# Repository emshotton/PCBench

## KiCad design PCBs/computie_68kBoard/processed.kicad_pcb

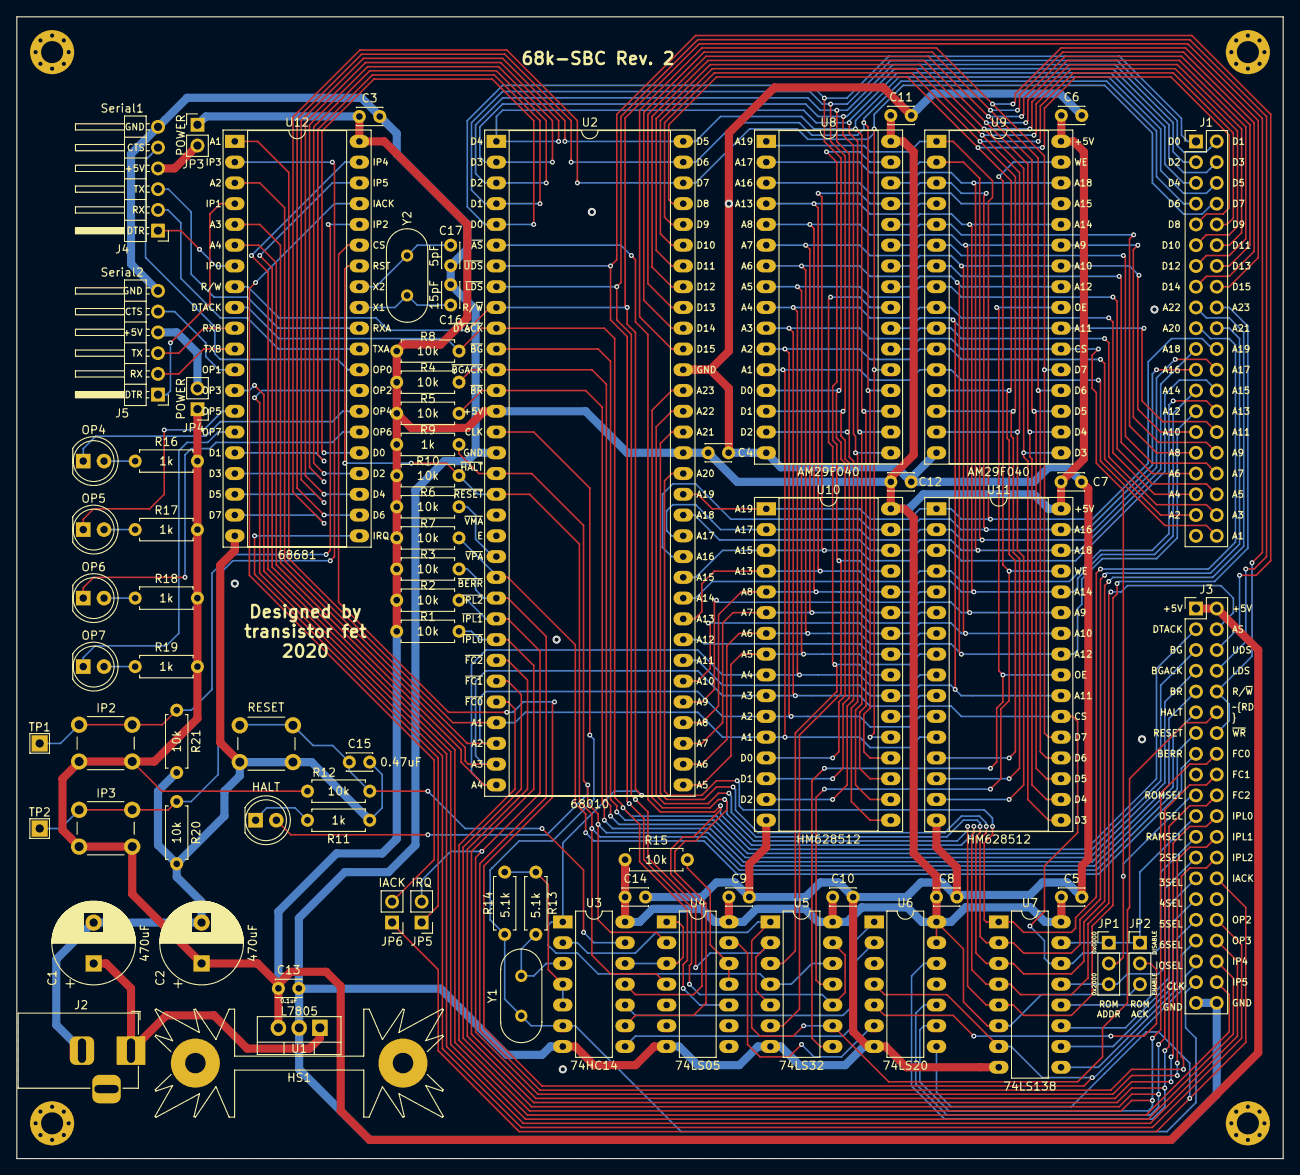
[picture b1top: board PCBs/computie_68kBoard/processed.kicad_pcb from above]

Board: 2 copper layers, 154.9 x 139.7 mm, 78 parts (0 on the bottom side), 114 nets.

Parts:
C1, C2: 470uF; CP_Radial_D10.0mm_P5.00mm
C3, C4, C5, C6, C7, C8, C9, C10, C11, C12, C13, C14: 0.1uF; C_Disc_D3.0mm_W2.0mm_P2.50mm
C15: 0.47uF; C_Disc_D3.0mm_W2.0mm_P2.50mm
C16: 15pF; C_Disc_D3.0mm_W2.0mm_P2.50mm
C17: 5pF; C_Disc_D3.0mm_W2.0mm_P2.50mm
D1: HALT; LED_D5.0mm
D2: OP4; LED_D5.0mm
D3: OP5; LED_D5.0mm
D4: OP6; LED_D5.0mm
D5: OP7; LED_D5.0mm
H1, H2, H3, H4: .; MountingHole_2.7mm_Pad_Via
HS1: Heatsink; Heatsink_Fischer_SK104-STC-STIC_35x13mm_2xDrill2.5mm
J1: ADBUS; PinHeader_2x20_P2.54mm_Vertical
J2: Barrel_Jack; BarrelJack_Horizontal
J3: SIGBUS; PinHeader_2x20_P2.54mm_Vertical
J4: Serial1; PinHeader_1x06_P2.54mm_Horizontal
J5: Serial2; PinHeader_1x06_P2.54mm_Horizontal
JP1: ROMJMP; PinHeader_1x03_P2.54mm_Vertical
JP2: ROMACK; PinHeader_1x03_P2.54mm_Vertical
JP3, JP4: POWER; PinHeader_1x02_P2.54mm_Vertical
JP5: IRQ; PinHeader_1x02_P2.54mm_Vertical
JP6: IACK; PinHeader_1x02_P2.54mm_Vertical
R1, R2, R3, R4, R5, R6, R7, R8, R10, R12, R15, R20, R21: 10k; R_Axial_DIN0207_L6.3mm_D2.5mm_P7.62mm_Horizontal
R9, R11, R16, R17, R18, R19: 1k; R_Axial_DIN0207_L6.3mm_D2.5mm_P7.62mm_Horizontal
R13, R14: 5.1k; R_Axial_DIN0207_L6.3mm_D2.5mm_P7.62mm_Horizontal
SW1: RESET; SW_PUSH_6mm
SW2: IP2; SW_PUSH_6mm
SW3: IP3; SW_PUSH_6mm
TP1: IP2; TestPoint_THTPad_2.0x2.0mm_Drill1.0mm
TP2: IP3; TestPoint_THTPad_2.0x2.0mm_Drill1.0mm
U1: L7805; TO-220-3_Vertical
U2: 68010; DIP-64_W22.86mm_Socket_LongPads
U3: 74HC14; DIP-14_W7.62mm_LongPads
U4: 74LS05; DIP-14_W7.62mm_LongPads
U5: 74LS32; DIP-14_W7.62mm_LongPads
U6: 74LS20; DIP-14_W7.62mm_LongPads
U7: 74LS138; DIP-16_W7.62mm_LongPads
U8, U9: AM29F040; DIP-32_W15.24mm_Socket_LongPads
U10, U11: HM628512; DIP-32_W15.24mm_Socket_LongPads
U12: 68681; DIP-40_W15.24mm_Socket_LongPads
Y1, Y2: Crystal; Crystal_HC49-4H_Vertical

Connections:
0SEL: J3.21, JP1.1, JP2.1, U7.15
2SEL: J3.25, JP1.3, U7.13
3SEL: J3.27, U7.12
4SEL: J3.29, U7.11
5SEL: J3.31, U7.10
6SEL: J3.33, U7.9
+5V: C2.1, C3.1, C4.1, C5.1, C6.1, C7.1, C8.1, C9.1, C10.1, C11.1, C12.1, C13.1, C14.1, J3.1, J3.2, JP2.3, JP3.1, JP4.1, R1.1, R2.1, R3.1, R4.1, R5.1, R6.1, R7.1, R8.1, R9.1, R10.1, R12.1, R15.1, R16.2, R17.2, R18.2, R19.2, SW2.2, SW3.2, U1.3, U2.14, U2.49, U3.14, U4.14, U5.14, U6.13, U6.14, U7.6, U7.16, U8.32, U9.32, U10.32, U11.32, U12.40
A1: J1.40, U2.29, U8.12, U9.12, U10.12, U11.12, U12.1
A2: J1.37, U2.30, U8.11, U9.11, U10.11, U11.11, U12.3
A3: J1.38, U2.31, U8.10, U9.10, U10.10, U11.10, U12.5
A4: J1.35, U2.32, U8.9, U9.9, U10.9, U11.9, U12.6
A5: J1.36, U2.33, U8.8, U9.8, U10.8, U11.8
A6: J1.33, U2.34, U8.7, U9.7, U10.7, U11.7
A7: J1.34, U2.35, U8.6, U9.6, U10.6, U11.6
A8: J1.31, U2.36, U8.5, U9.5, U10.5, U11.5
A9: J1.32, U2.37, U8.27, U9.27, U10.27, U11.27
A10: J1.29, U2.38, U8.26, U9.26, U10.26, U11.26
A11: J1.30, U2.39, U8.23, U9.23, U10.23, U11.23
A12: J1.27, U2.40, U8.25, U9.25, U10.25, U11.25
A13: J1.28, U2.41, U8.4, U9.4, U10.4, U11.4
A14: J1.25, U2.42, U8.28, U9.28, U10.28, U11.28
A15: J1.26, U2.43, U8.29, U9.29, U10.3, U11.3
A16: J1.23, U2.44, U8.3, U9.3, U10.31, U11.31
A17: J1.24, U2.45, U8.2, U9.2, U10.2, U11.2
A18: J1.21, U2.46, U8.30, U9.30, U10.30, U11.30
A19: J1.22, U2.47, U8.1, U9.1, U10.1, U11.1
A20: J1.19, U2.48, U7.1
A21: J1.20, U2.50, U7.2
A22: J1.17, U2.51, U7.3
A23: J1.18, U2.52, U3.9, U7.5
AS: J3.4, U2.6, U3.11, U7.4
BERR: J3.15, R7.2, U2.22
BG: J3.5, U2.11
BGACK: J3.7, R4.2, U2.12
BR: J3.9, R5.2, U2.13
CLK: J3.37, R14.1, U2.15, U3.6, Y1.2
D0: J1.1, U2.5, U8.13, U10.13, U12.25
D1: J1.2, U2.4, U8.14, U10.14, U12.16
D2: J1.3, U2.3, U8.15, U10.15, U12.24
D3: J1.4, U2.2, U8.17, U10.17, U12.17
D4: J1.5, U2.1, U8.18, U10.18, U12.23
D5: J1.6, U2.64, U8.19, U10.19, U12.18
D6: J1.7, U2.63, U8.20, U10.20, U12.22
D7: J1.8, U2.62, U8.21, U10.21, U12.19
D8: J1.9, U2.61, U9.13, U11.13
D9: J1.10, U2.60, U9.14, U11.14
D10: J1.11, U2.59, U9.15, U11.15
D11: J1.12, U2.58, U9.17, U11.17
D12: J1.13, U2.57, U9.18, U11.18
D13: J1.14, U2.56, U9.19, U11.19
D14: J1.15, U2.55, U9.20, U11.20
D15: J1.16, U2.54, U9.21, U11.21
DTACK: J3.3, R8.2, U2.10, U4.10, U12.9
FC0: J3.16, U2.28, U6.9
FC1: J3.18, U2.27, U6.10
FC2: J3.20, U2.26, U6.12
GND: C1.2, C2.2, C3.2, C4.2, C5.2, C6.2, C7.2, C8.2, C9.2, C10.2, C11.2, C12.2, C13.2, C14.2, C15.2, C16.1, C17.1, J2.2, J3.39, J3.40, J4.6, J5.6, R11.2, R20.2, R21.2, SW1.1, U1.2, U2.16, U2.53, U3.7, U4.7, U5.7, U6.7, U7.8, U8.16, U9.16, U10.16, U11.16, U12.20
HALT: D1.2, J3.11, R9.2, U2.17, U4.2
IACK: J3.28, JP6.1, U6.8
IOSEL: J3.35, U6.4, U7.7, U12.35
IP4: J3.36, U12.39
IP5: J3.38, U12.38
IPL0: J3.22, R1.2, U2.25
IPL1: J3.24, JP5.2, R2.2, U2.24
IPL2: J3.26, R3.2, U2.23
LDS: J3.8, U2.8, U5.2, U5.5
unnamed: C1.1, J2.1, U1.1
unnamed: C15.1, R12.2, SW1.2, U3.13
unnamed: C16.2, U12.32, Y2.2
unnamed: C17.2, U12.33, Y2.1
unnamed: D1.1, R11.1
unnamed: D2.1, U12.27
unnamed: D2.2, R16.1
unnamed: D3.1, U12.14
unnamed: D3.2, R17.1
unnamed: D4.1, U12.26
unnamed: D4.2, R18.1
unnamed: D5.1, U12.15
unnamed: D5.2, R19.1
unnamed: J4.1, U12.7
unnamed: J4.2, U12.30
unnamed: J4.3, U12.31
unnamed: J4.4, JP3.2
unnamed: J4.5, U12.29
unnamed: J5.1, U12.4
unnamed: J5.2, U12.11
unnamed: J5.3, U12.10
unnamed: J5.4, JP4.2
unnamed: J5.5, U12.12
unnamed: JP2.2, U6.5
unnamed: R6.2, U2.21
unnamed: R13.1, R14.2, U3.4, U3.5
unnamed: R13.2, U3.3, Y1.1
unnamed: R15.2, U4.11, U4.12
unnamed: R20.1, SW3.1, TP2.1, U12.2
unnamed: R21.1, SW2.1, TP1.1, U12.36
unnamed: U3.8, U6.2
unnamed: U3.10, U6.1
unnamed: U3.12, U4.1, U4.3
unnamed: U4.13, U6.6
OP2: J3.32, U12.28
OP3: J3.34, U12.13
RAMSEL: J3.23, U7.14, U10.22, U11.22
RD: J3.12, U3.2, U5.1, U5.9
RD-L: U5.3, U8.24, U10.24
RD-U: U5.8, U9.24, U11.24
RESET: J3.13, R10.2, U2.18, U4.4, U12.34
ROMSEL: J3.19, JP1.2, U8.22, U9.22
R~W: J3.10, J3.14, U2.9, U3.1, U5.4, U5.12, U12.8
SIACK: JP6.2, U12.37
SIRQ: JP5.1, U12.21
UDS: J3.6, U2.7, U5.10, U5.13
WR-L: U5.6, U8.31, U10.29
WR-U: U5.11, U9.31, U11.29

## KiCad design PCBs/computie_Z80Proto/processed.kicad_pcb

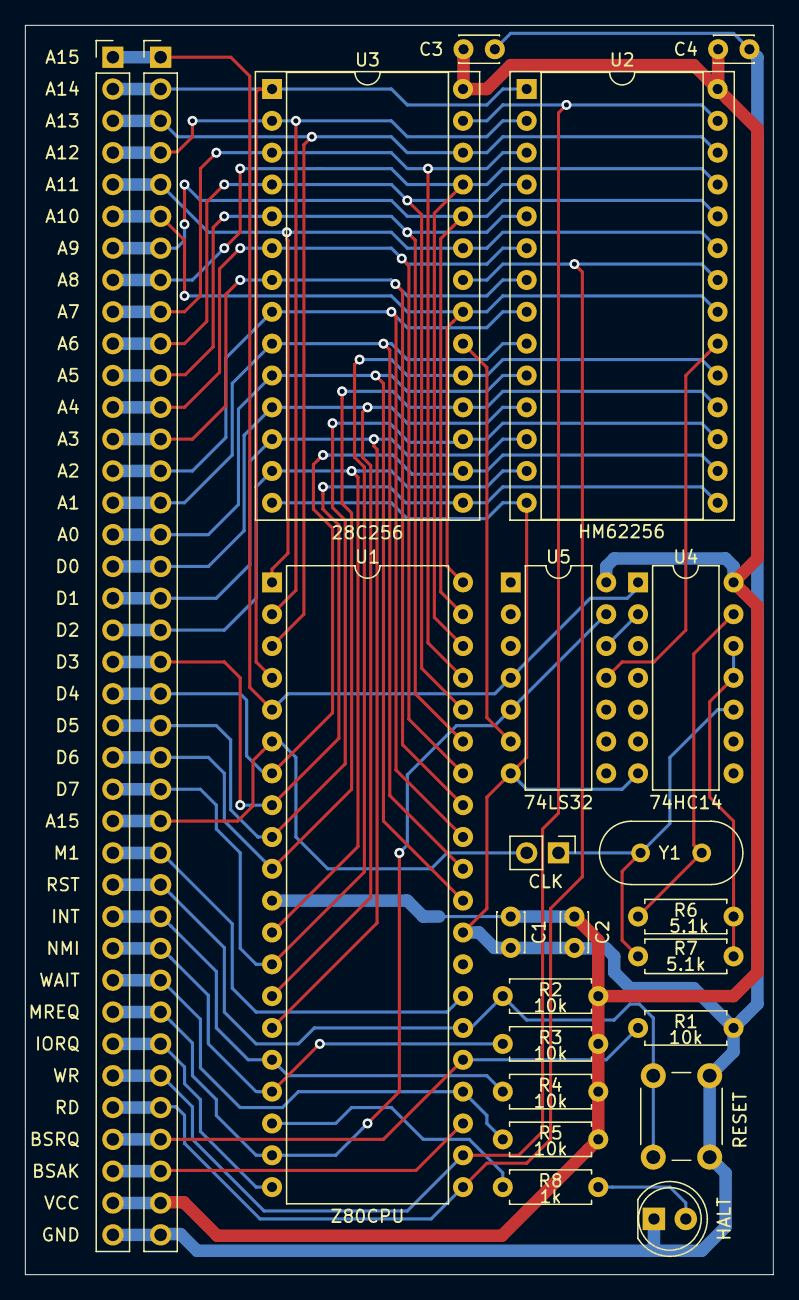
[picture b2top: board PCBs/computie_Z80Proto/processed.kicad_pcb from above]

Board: 2 copper layers, 59.7 x 99.7 mm, 23 parts (0 on the bottom side), 46 nets.

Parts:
B1: RESET; SW_PUSH_6mm
C1, C3, C4: 0.1uF; C_Disc_D3.0mm_W2.0mm_P2.50mm
C2: 0.47uF; C_Disc_D3.0mm_W2.0mm_P2.50mm
J1, J1#2: Conn_01x38; PinHeader_1x38_P2.54mm_Vertical
JP1: CLK; PinHeader_1x02_P2.54mm_Vertical
LED1: HALT; LED_D5.0mm
R1, R2, R3, R4, R5: 10k; R_Axial_DIN0207_L6.3mm_D2.5mm_P7.62mm_Horizontal
R6, R7: 5.1k; R_Axial_DIN0207_L6.3mm_D2.5mm_P7.62mm_Horizontal
R8: 1k; R_Axial_DIN0207_L6.3mm_D2.5mm_P7.62mm_Horizontal
U1: Z80CPU; DIP-40_W15.24mm
U2: HM62256; DIP-28_W15.24mm_Socket
U3: 28C256; DIP-28_W15.24mm_Socket
U4: 74HC14; DIP-14_W7.62mm
U5: 74LS32; DIP-14_W7.62mm
Y1: Crystal; Crystal_HC49-4H_Vertical

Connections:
/A0: J1.16, J1#2.16, U1.30, U2.10, U3.10
/A1: J1.15, J1#2.15, U1.31, U2.9, U3.9
/A2: J1.14, J1#2.14, U1.32, U2.8, U3.8
/A3: J1.13, J1#2.13, U1.33, U2.7, U3.7
/A4: J1.12, J1#2.12, U1.34, U2.6, U3.6
/A5: J1.11, J1#2.11, U1.35, U2.5, U3.5
/A6: J1.10, J1#2.10, U1.36, U2.4, U3.4
/A7: J1.9, J1#2.9, U1.37, U2.3, U3.3
/A8: J1.8, J1#2.8, U1.38, U2.25, U3.25
/A9: J1.7, J1#2.7, U1.39, U2.24, U3.24
/A10: J1.6, J1#2.6, U1.40, U2.21, U3.21
/A11: J1.5, J1#2.5, U1.1, U2.23, U3.23
/A12: J1.4, J1#2.4, U1.2, U2.2, U3.2
/A13: J1.3, J1#2.3, U1.3, U2.26, U3.26
/A14: J1.2, J1#2.2, U1.4, U2.1, U3.1
/A15: J1.1, J1#2.1, U1.5, U4.1, U5.4
/D0: J1.17, J1#2.17, U1.14, U2.11, U3.11
/D1: J1.18, J1#2.18, U1.15, U2.12, U3.12
/D2: J1.19, J1#2.19, U1.12, U2.13, U3.13
/D3: J1.20, J1#2.20, U1.8, U2.15, U3.15
/D4: J1.21, J1#2.21, U1.7, U2.16, U3.16
/D5: J1.22, J1#2.22, U1.9, U2.17, U3.17
/D6: J1.23, J1#2.23, U1.10, U2.18, U3.18
/D7: J1.24, J1#2.24, U1.13, U2.19, U3.19
BUSACK: J1.36, J1#2.36, U1.23
BUSREQ: J1.35, J1#2.35, R1.1, U1.25
CLK: J1.25, J1#2.25, JP1.2, U1.6
GND: B1.1, C1.2, C2.2, C3.2, C4.2, J1.38, J1#2.38, LED1.1, R1.2, U1.29, U2.14, U3.14, U4.7, U5.7
HALT: R8.1, U1.18
INT: J1.28, J1#2.28, R4.2, U1.16
IOREQ: J1.32, J1#2.32, U1.20
M1: J1.26, J1#2.26, U1.27
MREQ: J1.31, J1#2.31, U1.19, U5.5, U5.13
NMI: J1.29, J1#2.29, R3.2, U1.17
unnamed: JP1.1, R7.1, U4.10, Y1.2
unnamed: LED1.2, R8.2
unnamed: R6.1, R7.2, U4.11, U4.12
unnamed: R6.2, U4.13, Y1.1
unnamed: U2.20, U5.11
unnamed: U3.20, U5.6
unnamed: U4.2, U5.12
RD: J1.34, J1#2.34, U1.21, U2.22, U3.22
RESET: B1.2, J1.27, J1#2.27, R2.2, U1.26
Vcc: C1.1, C2.1, C3.1, C4.1, J1.37, J1#2.37, R2.1, R3.1, R4.1, R5.1, U1.11, U2.28, U3.28, U4.14, U5.14
WAIT: J1.30, J1#2.30, R5.2, U1.24
WR: J1.33, J1#2.33, U1.22, U2.27, U3.27

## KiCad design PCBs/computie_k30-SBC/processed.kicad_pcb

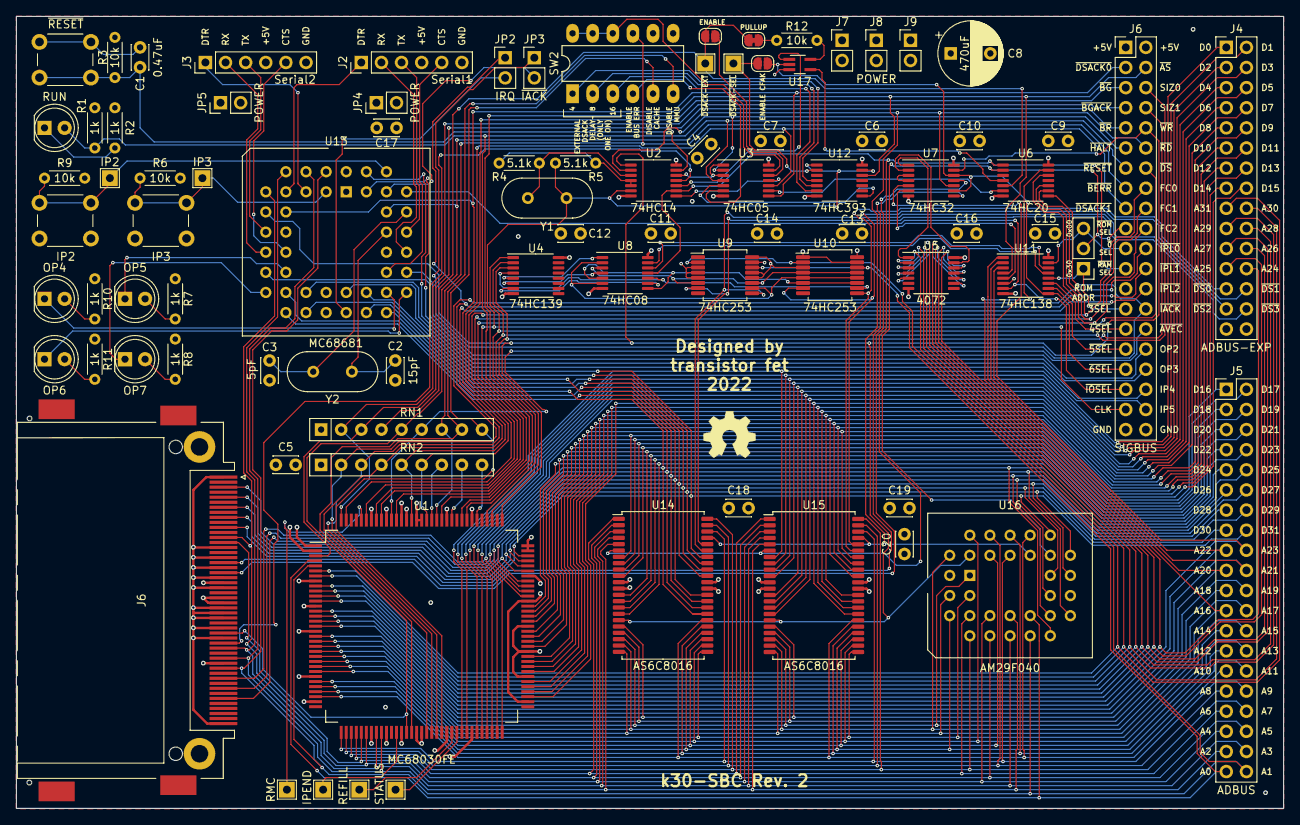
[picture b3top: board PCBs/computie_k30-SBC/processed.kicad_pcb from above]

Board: 4 copper layers, 160.0 x 100.0 mm, 87 parts (0 on the bottom side), 173 nets.

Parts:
C1: 0.47uF; C_Disc_D3.0mm_W2.0mm_P2.50mm
C2: 15pF; C_Disc_D3.0mm_W2.0mm_P2.50mm
C3: 5pF; C_Disc_D3.0mm_W2.0mm_P2.50mm
C4, C5, C6, C7, C9, C10, C11, C12, C13, C14, C15, C16, C17, C18, C19, C20: 0.1uF; C_Disc_D3.0mm_W2.0mm_P2.50mm
C8: 470uF; CP_Radial_D8.0mm_P5.00mm
D1: RUN; LED_D5.0mm
D2: OP5; LED_D5.0mm
D3: OP7; LED_D5.0mm
D4: OP4; LED_D5.0mm
D5: OP6; LED_D5.0mm
J1: CompactFlash; CF-Card_3M_N7E50-Q516RB-40
J2: Serial1; PinHeader_1x06_P2.54mm_Vertical
J3: Serial2; PinHeader_1x06_P2.54mm_Vertical
J4: ADBUS-EXP; PinHeader_2x15_P2.54mm_Vertical
J5: ADBUS; PinHeader_2x20_P2.54mm_Vertical
J6: SIGBUS; PinHeader_2x20_P2.54mm_Vertical
J7, J8, J9: POWER; PinHeader_1x02_P2.54mm_Vertical
JP1: ROMJMP; PinHeader_1x03_P2.54mm_Vertical
JP2: IRQ; PinHeader_1x02_P2.54mm_Vertical
JP3: ~{IACK}; PinHeader_1x02_P2.54mm_Vertical
JP4, JP5: POWER; PinHeader_1x02_P2.54mm_Vertical
JP6: ENABLE; SolderJumper-2_P1.3mm_Open_RoundedPad1.0x1.5mm
JP7: PULLUP; SolderJumper-2_P1.3mm_Bridged_RoundedPad1.0x1.5mm
JP8: ENABLE CFAK; SolderJumper-2_P1.3mm_Open_RoundedPad1.0x1.5mm
R1, R2, R7, R8, R10, R11: 1k; R_Axial_DIN0204_L3.6mm_D1.6mm_P5.08mm_Horizontal
R3, R6, R9, R12: 10k; R_Axial_DIN0204_L3.6mm_D1.6mm_P5.08mm_Horizontal
R4, R5: 5.1k; R_Axial_DIN0204_L3.6mm_D1.6mm_P5.08mm_Horizontal
RN1, RN2: 10k; R_Array_SIP9
SW1: ~{RESET}; SW_PUSH_6mm
SW2: SW_DIP_x06; DIP-12_W7.62mm_LongPads
SW3: IP2; SW_PUSH_6mm
SW4: IP3; SW_PUSH_6mm
TP1: IPEND; TestPoint_THTPad_2.0x2.0mm_Drill1.0mm
TP2: REFILL; TestPoint_THTPad_2.0x2.0mm_Drill1.0mm
TP3: STATUS; TestPoint_THTPad_2.0x2.0mm_Drill1.0mm
TP4: ~{DSACK-EXT}; TestPoint_THTPad_2.0x2.0mm_Drill1.0mm
TP5: IP3; TestPoint_THTPad_2.0x2.0mm_Drill1.0mm
TP6: IP2; TestPoint_THTPad_2.0x2.0mm_Drill1.0mm
TP7: RMC; TestPoint_THTPad_2.0x2.0mm_Drill1.0mm
TP8: ~{DSACK-SEL}; TestPoint_THTPad_2.0x2.0mm_Drill1.0mm
U1: MC68030FE; PQFP-132_24x24mm_P0.635mm
U2: 74HC14; TSSOP-14_4.4x5mm_P0.65mm
U3: 74HC05; TSSOP-14_4.4x5mm_P0.65mm
U4: 74HC139; TSSOP-16_4.4x5mm_P0.65mm
U5: 4072; TSSOP-14_4.4x5mm_P0.65mm
U6: 74HC20; TSSOP-14_4.4x5mm_P0.65mm
U7: 74HC32; TSSOP-14_4.4x5mm_P0.65mm
U8: 74HC08; TSSOP-14_4.4x5mm_P0.65mm
U9, U10: 74HC253; SSOP-16_5.3x6.2mm_P0.65mm
U11: 74HC138; TSSOP-16_4.4x5mm_P0.65mm
U12: 74HC393; TSSOP-14_4.4x5mm_P0.65mm
U13: MC68681; PLCC-44_THT-Socket
U14, U15: AS6C8016; TSOP-II-44_10.16x18.41mm_P0.8mm
U16: AM29F040; PLCC-32_THT-Socket
U17: 74LVC1G32; SOT-353_SC-70-5_Handsoldering
Y1, Y2: Crystal; Crystal_HC49-4H_Vertical

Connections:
+5V: C4.1, C5.1, C6.1, C7.1, C8.1, C9.1, C10.1, C11.1, C12.1, C13.1, C14.1, C15.1, C16.1, C17.1, C18.1, C19.1, C20.1, J1.13, J1.36, J1.38, J1.44, J6.1, J6.2, J7.1, J8.1, J9.1, JP4.1 (A), JP5.1 (A), R1.2, R3.1, R7.2, R8.2, R10.2, R11.2, R12.1, RN1.1 (common), RN2.1 (common), SW3.2, SW4.2, U1.1 (VCC), U1.13 (VCC), U1.32 (VCC), U1.46 (VCC), U1.55 (VCC), U1.68 (VCC), U1.88 (VCC), U1.98 (VCC), U1.99 (VCC), U1.111 (VCC), U1.119 (VCC), U1.123 (VCC), U2.14 (VCC), U3.14 (VCC), U4.16 (VCC), U5.14 (VDD), U6.14 (VCC), U7.14 (VCC), U8.14 (VCC), U9.3 (I3a), U9.4 (I2a), U9.5 (I1a), U9.12 (I2b), U9.13 (I3b), U9.16 (VCC), U10.3 (I3a), U10.16 (VCC), U11.6 (E3), U11.16 (VCC), U12.14 (VCC), U13.44 (VCC), U14.11 (VCC), U14.33 (VCC), U15.11 (VCC), U15.33 (VCC), U16.32 (VCC), U17.5 (VCC)
A0: J5.39, U1.4 (A0), U9.14 (A0), U10.14 (A0), U16.12 (A0)
A1: J1.20, J5.40, U1.5 (A1), U9.2 (A1), U10.2 (A1), U13.2 (RS1), U16.11 (A1)
A2: J1.19, J5.37, U1.42 (A2), U13.4 (RS2), U14.5 (A0), U15.5 (A0), U16.10 (A2)
A3: J1.18, J5.38, U1.41 (A3), U13.6 (RS3), U14.4 (A1), U15.4 (A1), U16.9 (A3)
A4: J1.7, J5.35, U1.39 (A4), U13.7 (RS4), U14.3 (A2), U15.3 (A2), U16.8 (A4)
A5: J1.32, J5.36, U1.38 (A5), U14.2 (A3), U15.2 (A3), U16.7 (A5)
A6: J5.33, U1.37 (A6), U14.1 (A4), U15.1 (A4), U16.6 (A6)
A7: J5.34, U1.36 (A7), U14.44 (A5), U15.44 (A5), U16.5 (A7)
A8: J5.31, U1.35 (A8), U14.43 (A6), U15.43 (A6), U16.27 (A8)
A9: J5.32, U1.34 (A9), U14.42 (A7), U15.42 (A7), U16.26 (A9)
A10: J5.29, U1.31 (A10), U14.28 (A8), U15.28 (A8), U16.23 (A10)
A11: J5.30, U1.30 (A11), U14.27 (A9), U15.27 (A9), U16.25 (A11)
A12: J5.27, U1.29 (A12), U14.26 (A10), U15.26 (A10), U16.4 (A12)
A13: J5.28, U1.28 (A13), U14.25 (A11), U15.25 (A11), U16.28 (A13)
A14: J5.25, U1.26 (A14), U14.24 (A12), U15.24 (A12), U16.29 (A14)
A15: J5.26, U1.25 (A15), U14.23 (A13), U15.23 (A13), U16.3 (A15)
A16: J5.23, U1.24 (A16), U6.13, U14.22 (A14), U15.22 (A14), U16.2 (A16)
A17: J5.24, U1.23 (A17), U14.21 (A15), U15.21 (A15), U16.30 (A17)
A18: J5.21, U1.22 (A18), U14.20 (A16), U15.20 (A16), U16.1 (A18)
A19: J5.22, U1.21 (A19), U14.19 (A17), U15.19 (A17)
A20: J5.19, U1.20 (A20), U11.1 (A0), U14.18 (A18), U15.18 (A18)
A21: J5.20, U1.19 (A21), U11.2 (A1)
A22: J5.17, U1.17 (A22), U11.3 (A2)
A23: J5.18, U1.16 (A23), U7.5
A24: J4.24, U1.15 (A24), U5.12
A25: J4.23, U1.14 (A25), U5.11
A26: J4.22, U1.12 (A26), U5.10
A27: J4.21, U1.11 (A27), U5.9
A28: J4.20, U1.10 (A28), U5.5
A29: J4.19, U1.9 (A29), U5.4
A30: J4.18, U1.7 (A30), U5.3
A31: J4.17, U1.6 (A31), U5.2
ATA-READY: J1.42, U2.11
CLK: J6.37, R5.1, U1.121 (CLK), U2.6, U12.1 (CP), U12.13 (CP), Y1.2
D0: J4.1, U1.58 (D0), U15.7 (Q0)
D1: J4.2, U1.59 (D1), U15.8 (Q1)
D2: J4.3, U1.61 (D2), U15.9 (Q2)
D3: J4.4, U1.62 (D3), U15.10 (Q3)
D4: J4.5, U1.63 (D4), U15.13 (Q4)
D5: J4.6, U1.64 (D5), U15.14 (Q5)
D6: J4.7, U1.65 (D6), U15.15 (Q6)
D7: J4.8, U1.66 (D7), U15.16 (Q7)
D8: J4.9, U1.69 (D8), U15.29 (Q8)
D9: J4.10, U1.70 (D9), U15.30 (Q9)
D10: J4.11, U1.71 (D10), U15.31 (Q10)
D11: J4.12, U1.72 (D11), U15.32 (Q11)
D12: J4.13, U1.74 (D12), U15.35 (Q12)
D13: J4.14, U1.75 (D13), U15.36 (Q13)
D14: J4.15, U1.76 (D14), U15.37 (Q14)
D15: J4.16, U1.77 (D15), U15.38 (Q15)
D16: J5.1, U1.79 (D16), U14.7 (Q0)
D17: J5.2, U1.80 (D17), U14.8 (Q1)
D18: J5.3, U1.81 (D18), U14.9 (Q2)
D19: J5.4, U1.82 (D19), U14.10 (Q3)
D20: J5.5, U1.84 (D20), U14.13 (Q4)
D21: J5.6, U1.85 (D21), U14.14 (Q5)
D22: J5.7, U1.86 (D22), U14.15 (Q6)
D23: J5.8, U1.87 (D23), U14.16 (Q7)
D24: J1.21, J5.9, U1.89 (D24), U13.28 (D0), U14.29 (Q8), U16.13 (Q0)
D25: J1.22, J5.10, U1.90 (D25), U13.18 (D1), U14.30 (Q9), U16.14 (Q1)
D26: J1.23, J5.11, U1.91 (D26), U13.27 (D2), U14.31 (Q10), U16.15 (Q2)
D27: J1.2, J5.12, U1.92 (D27), U13.19 (D3), U14.32 (Q11), U16.17 (Q3)
D28: J1.3, J5.13, U1.94 (D28), U13.26 (D4), U14.35 (Q12), U16.18 (Q4)
D29: J1.4, J5.14, U1.95 (D29), U13.20 (D5), U14.36 (Q13), U16.19 (Q5)
D30: J1.5, J5.15, U1.96 (D30), U13.25 (D6), U14.37 (Q14), U16.20 (Q6)
D31: J1.6, J5.16, U1.97 (D31), U13.21 (D7), U14.38 (Q15), U16.21 (Q7)
FC0: J6.16, U1.127 (FC0), U6.9
FC1: J6.18, U1.125 (FC1), U6.10
FC2: J6.20, U1.124 (FC2), U6.12
GND: C1.2, C2.1, C3.1, C4.2, C5.2, C6.2, C7.2, C8.2, C9.2, C10.2, C11.2, C12.2, C13.2, C14.2, C15.2, C16.2, C17.2, C18.2, C19.2, C20.2, J1.1, J1.8, J1.9, J1.10, J1.11, J1.12, J1.14, J1.15, J1.16, J1.17, J1.39, J1.50, J2.6, J3.6, J6.39, J6.40, J7.2, J8.2, J9.2, R2.1, R6.2, R9.2, SW1.1, SW2.7, SW2.8, U1.2 (GND), U1.8 (GND), U1.18 (GND), U1.27 (GND), U1.40 (GND), U1.43 (GND), U1.49 (GND), U1.50 (GND), U1.60 (GND), U1.73 (GND), U1.78 (GND), U1.83 (GND), U1.93 (GND), U1.106 (GND), U1.116 (GND), U1.117 (GND), U1.120 (GND), U1.126 (GND), U2.7 (GND), U3.7 (GND), U4.8 (GND), U5.7 (VSS), U6.7 (GND), U7.7 (GND), U8.7 (GND), U9.1 (OEa), U9.8 (GND), U9.15 (OEb), U10.1 (OEa), U10.8 (GND), U10.15 (OEb), U11.8 (GND), U12.7 (GND), U13.22 (GND), U14.12 (VSS), U14.34 (VSS), U15.12 (VSS), U15.34 (VSS), U16.16 (GND), U17.3 (GND)
IP4: J6.36, U13.43 (IP4)
IP5: J6.38, U13.42 (IP5)
unnamed: C1.1, R3.2, SW1.2, U2.13
unnamed: C2.2, U13.36 (X1/CLK), Y2.2
unnamed: C3.2, U13.37 (X2), Y2.1
unnamed: D1.1 (K), R2.2
unnamed: D2.1 (K), U13.16 (OP5)
unnamed: D2.2 (A), R7.1
unnamed: D3.1 (K), U13.17 (OP7)
unnamed: D3.2 (A), R8.1
unnamed: D4.1 (K), U13.30 (OP4)
unnamed: D4.2 (A), R10.1
unnamed: D5.1 (K), U13.29 (OP6)
unnamed: D5.2 (A), R11.1
unnamed: J2.1, U13.8 (IP0)
unnamed: J2.2, U13.33 (TXDA)
unnamed: J2.3, U13.35 (RXDA)
unnamed: J2.4, JP4.2 (B)
unnamed: J2.5, U13.32 (OP0)
unnamed: J3.1, U13.5 (IP1)
unnamed: J3.2, U13.13 (TXDB)
unnamed: J3.3, U13.11 (RXDB)
unnamed: J3.4, JP5.2 (B)
unnamed: J3.5, U13.14 (OP1)
unnamed: JP6.1 (A), U3.12
unnamed: JP7.2 (B), R12.2
unnamed: R4.1, R5.2, U2.4, U2.5
unnamed: R4.2, U2.3, Y1.1
unnamed: R6.1, SW4.1, TP5.1, U13.3 (IP3)
unnamed: R9.1, SW3.1, TP6.1, U13.40 (IP2)
unnamed: RN2.7 (R6), U1.114 (STERM)
unnamed: RN2.8 (R7), U1.110 (CBACK)
unnamed: RN2.9 (R8), U1.105 (CIIN)
unnamed: SW2.1, U12.4 (Q1)
unnamed: SW2.2, U12.5 (Q2)
unnamed: SW2.3, U12.6 (Q3)
unnamed: SW2.4, U3.6
unnamed: SW2.10, SW2.11, SW2.12, U3.13
unnamed: TP1.1, U1.45 (IPEND)
unnamed: TP2.1, U1.56 (REFILL)
unnamed: TP3.1, U1.57 (STATUS)
unnamed: TP7.1, U1.128 (RMC)
unnamed: JP8.2 (B), TP8.1, U12.2 (MR)
unnamed: U2.8, U3.11
unnamed: U2.12, U3.1, U3.3
unnamed: U3.9, U6.6
unnamed: U4.5 (O1), U8.1
unnamed: U4.6 (O2), U8.4
unnamed: U4.7 (O3), U8.9
unnamed: U5.1, U7.1
unnamed: U5.13, U7.2
unnamed: U7.3, U7.4
unnamed: U4.4 (O0), U8.10, U10.10 (I0b)
unnamed: U8.5, U8.8, U10.6 (I0a), U10.11 (I1b)
unnamed: U8.2, U8.6, U9.10 (I0b), U10.5 (I1a), U10.12 (I2b)
unnamed: U8.3, U9.6 (I0a), U9.11 (I1b), U10.4 (I2a), U10.13 (I3b)
unnamed: U7.6, U11.5 (E2)
unnamed: U8.13, U11.13 (O2)
unnamed: U8.12, U11.14 (O1)
unnamed: U3.5, U12.8 (Q3)
unnamed: U2.10, U17.1
OP2: J6.32, U13.31 (OP2)
OP3: J6.34, U13.15 (OP3)
SIZ0: J6.6, U1.103 (SIZ0), U4.2 (A0)
SIZ1: J6.8, U1.102 (SIZ1), U4.3 (A1)
~0SEL: J6.21, JP1.3 (B), U11.15 (O0)
~3SEL: J6.27, JP1.1 (A), U11.12 (O3)
~4SEL: J6.29, U11.11 (O4)
~5SEL: J6.31, U11.10 (O5)
~6SEL: J6.33, JP8.1 (A), U7.9, U7.12, U11.9 (O6), U17.2
~AS: J6.4, U1.108 (AS), U11.4 (E1), U12.12 (MR)
~ATA-DSACK: U6.4, U17.4
~AVEC: J6.30, RN1.6 (R5), U1.122 (AVEC)
~BERR: J6.15, RN1.7 (R6), SW2.9, U1.113 (BERR)
~BGACK: J6.7, RN1.2 (R1), U1.132 (BGACK)
~BG: J6.5, U1.131 (BG)
~BR: J6.9, RN1.3 (R2), U1.3 (BR)
~CDIS: RN1.9 (R8), SW2.5, U1.54 (CDIS)
~DS0: J4.25, U10.9 (Zb), U15.39 (~LB)
~DS1: J4.26, U10.7 (Za), U15.40 (~UB)
~DS2: J4.27, U9.9 (Zb), U14.39 (~LB)
~DS3: J4.28, U9.7 (Za), U14.40 (~UB)
~DSACK0: J6.3, RN2.5 (R4), U1.118 (DSACK0), U3.8, U13.10 (DTACK)
~DSACK1: J6.17, RN2.6 (R5), U1.115 (DSACK1), U3.10
~DSACK-EXT: JP6.2 (B), JP7.1 (A), RN1.4 (R3), TP4.1, U6.5
~DS: J6.14, U1.107 (DS), U4.1 (E)
~HALT: D1.2 (A), J6.11, R1.1, U1.112 (HALT), U3.2
~IACK: J6.28, JP3.1 (A), U6.8
~IORD: J1.34, U7.8
~IOSEL: J6.35, U11.7 (O7), U13.39 (CS)
~IOWR: J1.35, U7.11
~IPL0: J6.22, RN2.2 (R1), U1.53 (IPL0)
~IPL1: J6.24, JP2.1 (A), RN2.3 (R2), U1.52 (IPL1)
~IPL2: J6.26, RN2.4 (R3), U1.51 (IPL2)
~MMUDIS: RN1.8 (R7), SW2.6, U1.48 (MMUDIS)
~RAMSEL: J6.23, U2.9, U6.1, U8.11, U14.6 (~CE), U15.6 (~CE)
~RD: J6.12, U2.2, U7.10, U14.41 (~OE), U15.41 (~OE), U16.24 (~OE)
~RESET: J1.41, J6.13, RN1.5 (R4), U1.47 (RESET), U3.4, U13.38 (RESET)
~ROMSEL: J6.19, JP1.2 (C), U6.2, U16.22 (~CS)
~SIACK: JP3.2 (B), U13.41 (IACK)
~SIRQ: JP2.2 (B), U13.24 (IRQ)
~WR: J6.10, U1.100 (R/W), U2.1, U7.13, U13.9 (R/W), U14.17 (~WE), U15.17 (~WE), U16.31 (~WE)

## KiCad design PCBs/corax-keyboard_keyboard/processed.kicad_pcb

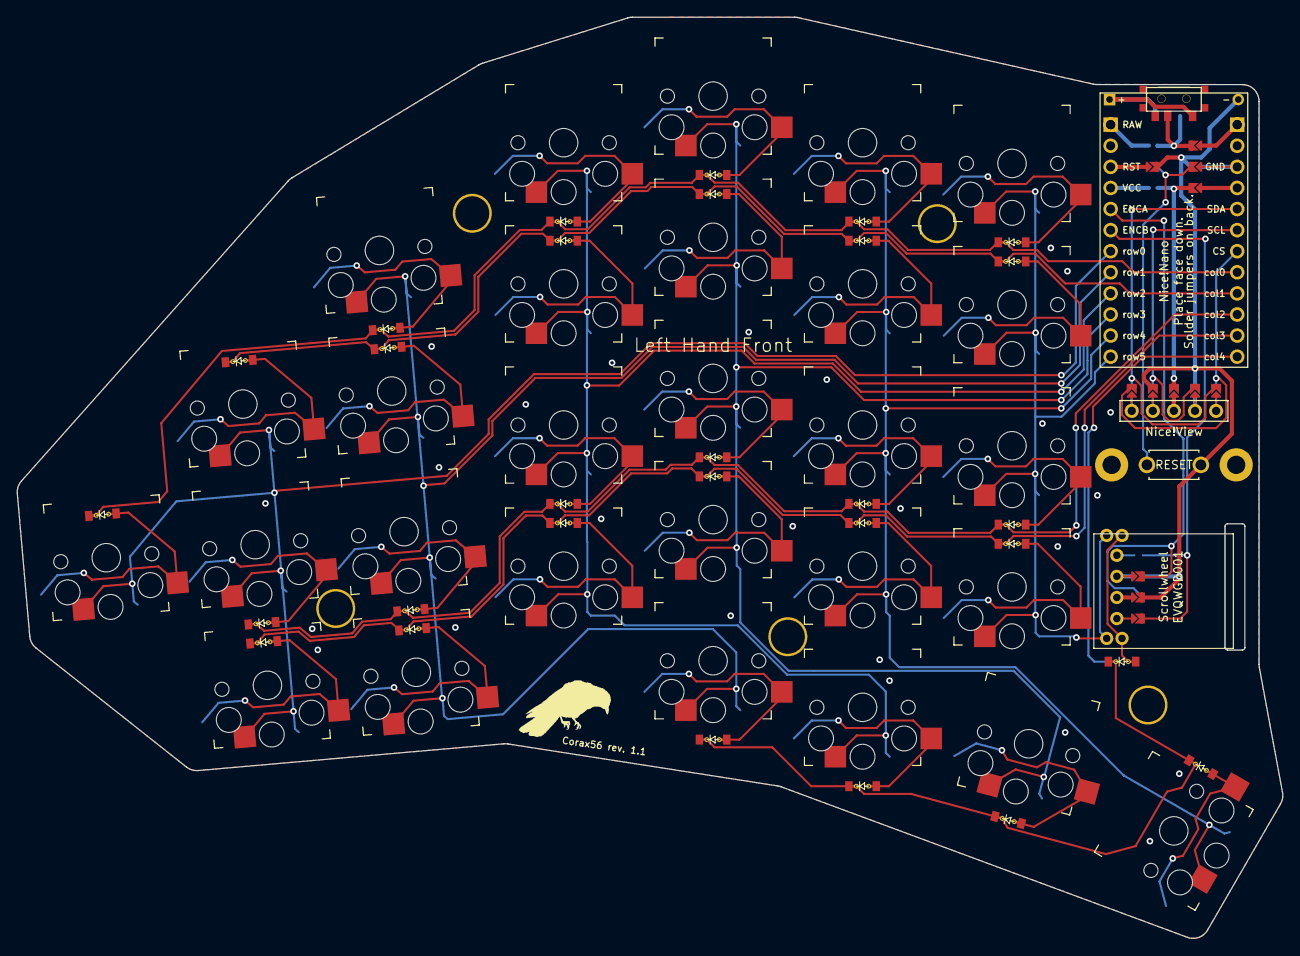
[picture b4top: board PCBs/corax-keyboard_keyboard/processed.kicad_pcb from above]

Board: 2 copper layers, 152.4 x 110.9 mm, 92 parts (0 on the bottom side), 61 nets.

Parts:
D1, D2, D3, D4, D5, D6, D7, D8, D9, D10, D11, D12, D13, D14, D15, D16, D17, D18, D19, D20, D21, D22, D23, D24, D25, D26, D27, D28, D29: ComboDiode
J1, J2, J3, J4, J5, J6, J7, J8, J9, J10, J11, J12, J13, J14, J15, J16, J17, J18, J19, J20, J21, J22, J23, J24: Jumper
MCU1: ProMicro
Nice!View1: niceview_headers
S1, S2, S3, S4, S5, S6, S7, S8, S9, S10, S11, S12, S13, S14, S15, S16, S17, S18, S19, S20, S21, S22, S23, S24, S25, S26, S27, S28: PG1350
T1: SPDT_C128955
_1: ResetSW
_2, _3, _4, _5, _6, _7, _8: Hole

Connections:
CS: J19.2, J24.2, MCU1.19
ENCA: J3.2, J6.2, MCU1.5
ENCA_GND: J3.1, J5.1
ENCB: J1.2, J4.2, MCU1.6
GND: J2.2, J5.2, J10.2, J14.2, J18.2, J23.2, _1.2
GND_ENCA: J2.1, J6.1
GND_RST: J10.1, J12.1, MCU1.15
GND_VCC: J13.1, MCU1.16
NN_CS_SDA: J19.1, J20.1, Nice!View1.1
NN_GND_SCL: J18.1, J21.1, Nice!View1.1
NN_SCL_GND: J16.1, J23.1, Nice!View1.3
NN_SDA_CS: J15.1, J24.1, Nice!View1.4
NN_VCC: J17.1, J22.1, Nice!View1.2
P1_RAW: J11.1, MCU1.13
RAW: J7.2, J11.2, T1.2
RAW_P1: J7.1, MCU1.1
RST: J8.2, J12.2, _1.1
RST_GND: J8.1, J14.1, MCU1.3
SCL: J16.2, J21.2, MCU1.18
SDA: J15.2, J20.2, MCU1.17
VCC: J9.2, J13.2, J17.2, J22.2
VCC_GND: J9.1, MCU1.4
col0: D3.1, D5.1, D8.1, D11.1, D13.1, D15.1, MCU1.20
col1: D17.1, D19.1, D21.1, D23.1, D25.1, D27.1, MCU1.21
col2: D1.1, D2.1, D4.1, D7.1, D10.1, D12.1, MCU1.22
col3: D16.1, D18.1, D20.1, D22.1, D24.1, D26.1, MCU1.23
col4: D6.1, D9.1, D14.1, D28.1, D29.1, MCU1.24
index_bottom: D24.2, S19.2
index_home: D10.2, S20.2
index_mod: D9.2, S18.2
index_num: D11.2, S22.2
index_top: D25.2, S21.2
inner_bottom: D26.2, S23.2
inner_home: D12.2, S24.2
inner_num: D13.2, S26.2
inner_top: D27.2, S25.2
layer_cluster: D14.2, S27.2
middle_bottom: D22.2, S14.2
middle_home: D7.2, S15.2
middle_mod: D6.2, S13.2
middle_num: D8.2, S17.2
middle_top: D23.2, S16.2
outer2_home: D15.2, S1.2
outer_bottom: D16.2, S2.2
outer_home: D1.2, S3.2
outer_top: D17.2, S4.2
pinky_bottom: D18.2, S5.2
pinky_home: D2.2, S6.2
pinky_num: D3.2, S8.2
pinky_top: D19.2, S7.2
ring_bottom: D20.2, S9.2
ring_home: D4.2, S10.2
ring_num: D5.2, S12.2
ring_top: D21.2, S11.2
row0: MCU1.7, S1.1, S2.1, S3.1, S4.1
row1: MCU1.8, S5.1, S6.1, S7.1, S8.1, S13.1
row2: MCU1.9, S9.1, S10.1, S11.1, S12.1, S18.1
row3: MCU1.10, S14.1, S15.1, S16.1, S17.1, S27.1
row4: MCU1.11, S19.1, S20.1, S21.1, S22.1, S28.1
row5: MCU1.12, S23.1, S24.1, S25.1, S26.1
space_cluster: D28.2, S28.2

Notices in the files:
PCBs/ergo-snm-keyboard_receiver/processed.kicad_pcb:
Open source hardware, CERN-OHL-P v2
parts and their libraries:
COPYRIGHT: Copyright 2019-2024 Great Scott Gadgets
LICENSE: Licensed under the CERN-OHL-P v2
